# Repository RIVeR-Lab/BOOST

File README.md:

# BOOST: Battery-Swapping Multi-Agent System for Sustained Operation of Large Planetary Fleets

## Abstract
We propose a novel, heterogeneous multi-agent architecture that miniaturizes rovers by outsourcing power generation to a central hub. By delegating power generation and distribution functions to this hub, the size, weight, power, and cost (SWAP-C) per rover are reduced, enabling efficient fleet scaling. As these rovers conduct mission tasks around the terrain, the hub charges an array of replacement battery modules. When a rover requires charging, it returns to the hub to initiate an autonomous docking sequence and exits with a fully charged battery. This confers an advantage over direct charging methods, such as wireless or wired charging, by replenishing a rover in minutes as opposed to hours, increasing net rover uptime.

This work shares an open-source platform developed to demonstrate battery swapping on unknown field terrain. We detail our design methodologies utilized for increasing system reliability, with a focus on optimization, robust mechanical design, and verification. Optimization of the system is discussed, including the design of passive guide rails through simulation-based optimization methods which increase the valid docking configuration space by 258%. The full system was evaluated during integrated testing, where an average servicing time of 98 seconds was achieved on surfaces with a gradient up to 10°. We conclude by briefly proposing flight considerations for advancing the system toward a space-ready design. In sum, this prototype represents a proof of concept for autonomous docking and battery transfer on field terrain, advancing its Technology Readiness Level (TRL) from 1 to 3.
## Building the system
[CAD models are available](https://river-lab.github.io/BOOST/CAD.html) in a wide variety of data formats. The mechanical hardware primarily consists of COTS components, 3D prints, and two large sheet metal plates; a [bill of materials](https://river-lab.github.io/BOOST/BOM.html) indicates what components were utilized. For the circuitry, [electronic schematics](https://river-lab.github.io/BOOST/ELECTRONICS.html) and [custom PCBs](electrical/) are both accessible.

## Installing Software
A [software overview](https://river-lab.github.io/BOOST/CODE.html) is provided. Further instructions can be found at [SOFTWARE.md](SOFTWARE.md).

## Links
- [Demo Video](https://www.youtube.com/watch?v=pb5BIy4iOmw)
- [Website](https://river-lab.github.io/BOOST/)
- [Paper (IEEEXplore)](https://ieeexplore.ieee.org/document/10521295)
- [Preprint (ArXiV)](https://arxiv.org/abs/2401.08497)

## Citing this work
```bibtex
@INPROCEEDINGS{10521295,
  author={Holand, Ethan and Homer, Jarrod and Storrer, Alex and Khandeker, Musheeera and Muhlon, Ethan F. and Patel, Maulik and Vainqueur, Ben-oni and Antaki, David and Cooke, Naomi and Wilson, Chloe and Shafai, Bahram and Hanson, Nathaniel and Padır, Taşkın},
  booktitle={2024 IEEE Aerospace Conference}, 
  title={Battery-Swapping Multi-Agent System for Sustained Operation of Large Planetary Fleets}, 
  year={2024},
  volume={},
  number={},
  pages={1-15},
  keywords={Wireless communication;Rails;Prototypes;Optimization methods;Batteries;Outsourcing;Reliability},
  doi={10.1109/AERO58975.2024.10521295}}
```

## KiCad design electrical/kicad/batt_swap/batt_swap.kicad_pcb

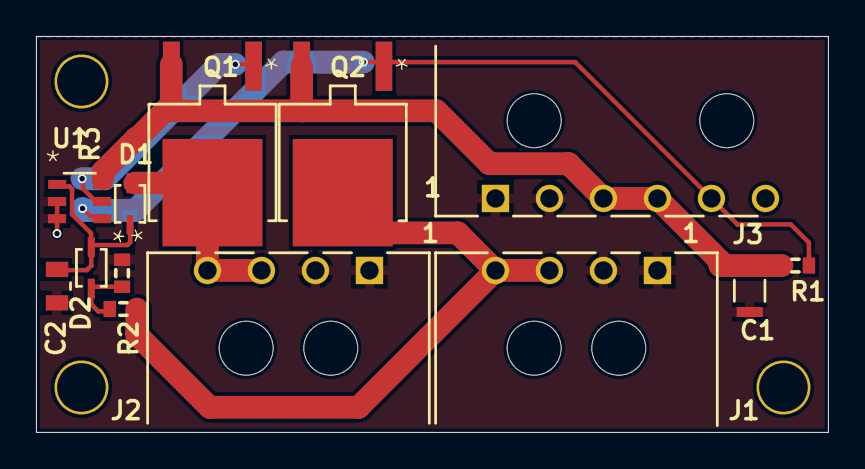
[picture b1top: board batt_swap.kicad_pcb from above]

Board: 2 copper layers, 44.0 x 22.0 mm, 13 parts (0 on the bottom side), 8 nets.

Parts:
C1: C2012JB1V226M125AC; CAP_2012_TDK
C2: CL21B105KBFNNNE; CAP_CL21_SAM
D1, D2: SD103AWS-7-F; SOD323_DIO
J1, J2: 436500400; CON_436500400_MOL
J3: 436500600; CON_436500600_MOL
Q1, Q2: AOD407; TO252_AOS
R1, R2, R3: Res3; J1-0603
U1: LTC4412ES6#TRPBF; LTC4412ES6#TRPBF_ADI

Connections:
GND: C1.1, C2.1, J1.1, J1.2, J2.1, J2.2, J3.1, J3.2, R3.1, U1.2, U1.3
NetC2_2: C2.2, D1.1, D2.1, U1.1
NetD2_2: D2.2, R2.1, R3.2
NetQ1_1: Q1.1, U1.5
batt: D1.2, J2.3, J2.4, Q1.3
hub: J1.3, J1.4, Q2.3, R2.2
stat: J3.5, Q2.1, R1.1, U1.4
vout: C1.2, J3.3, J3.4, Q1.2, Q2.2, R1.2, U1.6

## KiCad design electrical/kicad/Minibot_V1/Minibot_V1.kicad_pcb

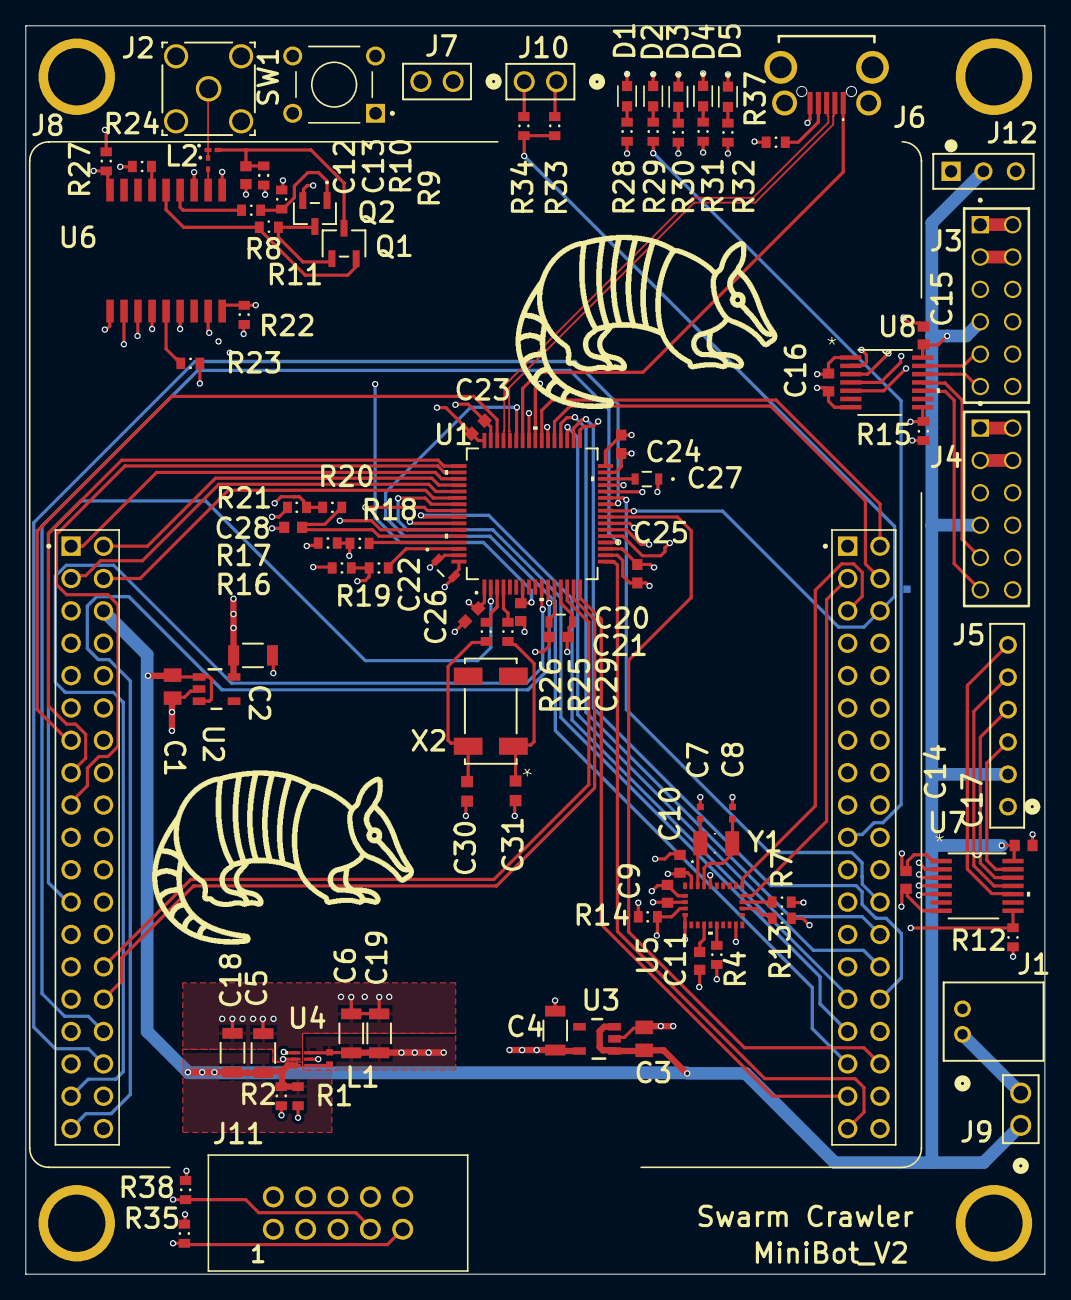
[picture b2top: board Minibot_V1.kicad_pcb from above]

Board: 6 copper layers, 80.0 x 98.0 mm, 97 parts (0 on the bottom side), 97 nets.

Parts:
C1, C3: GRM21BR71C475KE51L; CAP_GRM0805_2X1P25_MUR
C2, C4, C5, C6: CL31B106KOHNNWE; CAP_CL31_SAM
C7, C8: CBR04C220F5GAC; CAPC10555_55N_KEM
C9, C10, C11, C13, C14, C15, C16, C17: 0603; 1608[0603]
C12: C0603C0G1E270J030BA; CAP_0603_TDK
C18, C19: no stuff; CAP_CL31_SAM
C20: C1608X5R1C105K080AA; CAP_1608_TDK
C21, C23, C24, C25, C26: CC0603KRX7R7BB104; CC0603N_YAG
C22: C1608X5R1C475K080AC; CAP_1608_TDK
C27: C1608X5R1C225K080AB; CAP_1608_TDK
C28, C29: Cap Semi; 1608[0603]
C30, C31: GRM1885C1H4R3BA01D; CAPC1608X90N
D1, D2, D3, D4, D5: 150060SS75000; LED_150060SS75000
J1: S2B-PH-K-S(LF)(SN); CONN_S2B-PH-K-S_JST
J2: RF2-04A-T-00-50-G; CONN_RF2-04A-T-00-50-G_ADM
J3, J4: TSW-106-07-F-D; SAMTEC_TSW-106-07-F-D
J5: TSW-106-14-F-S; CON6_1X6_TU_TSW
J6: MCR-B-S-RA-SMT-CS14-T_R; MCRBSRASMTCS14TR
J7, J9, J10: 61300211121; CONN_61300211121_WRE
J8: NUCLEO-F446RE; MODULE_NUCLEO-F446RE
J11: 61201021621
J12: 22284036; 22-28-4036_MOL
L1: 1239AS-H-1R0M=P2; CAPC10555_55N_KEM
L2: MLG0603S36NJT000; IND_0603_TDK
Q1: AO3407A; SOT-23-3L_AOS
Q2: SMMBT3904LT1G; SOT-23-3_1P4X3P040_ONS
R1, R2, R4, R7, R8, R9, R10, R11, R12, R13, R14, R15, R16, R17, R18, R19, R20, R21, R27: 0603; J1-0603
R22, R23, R24, R25, R26, R28, R29, R30, R31, R32, R33, R34, R35, R37, R38: Res3; J1-0603
SW1: 1825910-2; TE_1825910-2
U1: STM32F446RCT6TR; LQFP64-10x10mm
U2, U3: LP2981-33DBVR; DBV0005A_N
U4: MP2148GQD-33-Z; QFN-1p0x1p5_MNP
U5: BNO055; QFN_BNO055_BOS
U6: GPS_FN; SL871
U7, U8: TXB0104PWR; PW14
X2: ABS25-32.768KHZ-1-T; ABS25-32.768KHZ-1-T_ABR
Y1: ECS-.327-12.5-34B-C-TR; XTAL_ECS-.327-12.5-34B-C-TR

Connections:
1PPS_GPS: J8.CN7_3, U1.53, U6.4
3V3: C6.2, C14.2, C16.2, C19.2, C20.2, C21.2, C22.2, C23.2, C24.2, C25.2, C26.2, J11.10, L1.2, R16.2, R17.2, R21.2, R35.2, U1.1, U1.13, U1.19, U1.32, U1.48, U1.64, U4.6, U7.1, U8.1
3V3_GPS: C2.2, R22.2, R24.1, U2.5, U6.6, U6.8
3V3_IMU: C4.2, C9.2, C10.2, R4.2, R14.2, U3.5, U5.3, U5.28
5V: C1.2, C3.2, C5.2, C15.2, C17.2, C18.2, J3.07, J4.07, J5.2, J8.CN7_6, J9.1, J12.A2, R1.2, R2.1, U2.1, U2.3, U3.1, U3.3, U4.3, U7.14, U8.14
ANT: C12.1, J2.1, L2.1
BATT_VIN: J10.1, R33.1
BATT_VOL: J8.CN10_6, R33.2, R34.1, U1.25
BOOT_IMU: J8.CN10_22, R14.1, U1.28, U5.4
D_N: J6.2, U1.44
D_P: J6.3, U1.45
ENC_1_A_5V: J3.09, U8.13
ENC_1_B_5V: J3.11, U8.12
ENC_2_A_5V: J4.09, U8.11
ENC_2_B_5V: J4.11, U8.10
FORCE_ON_N: J8.CN7_4, R27.2, U1.54, U6.18
GND: C1.1, C2.1, C3.1, C4.1, C5.1, C6.1, C7.2, C8.2, C9.1, C10.1, C11.1, C13.1, C14.1, C15.1, C16.1, C17.1, C18.1, C19.1, C20.1, C21.1, C22.1, C23.1, C24.1, C25.1, C26.1, C27.1, C28.1, C29.1, C30.2, C31.2, D1.1, D2.1, D3.1, D4.1, D5.1, J1.2, J2.2, J2.3, J2.4, J2.5, J3.05, J4.05, J5.1, J6.5, J6.MH1, J6.MH2, J6.MH3, J6.MH4, J7.2, J8.CN7_8, J8.CN7_19, J8.CN7_20, J8.CN7_22, J8.CN10_9, J8.CN10_20, J10.2, J11.2, J11.6, J11.8, J12.A3, Q2.2, R7.1, R9.1, R10.1, R12.1, R13.1, R15.1, R23.1, R27.1, R34.2, R37.1, R38.1, SW1.3, U1.12, U1.18, U1.31, U1.47, U1.63, U2.2, U3.2, U4.2, U5.2, U5.5, U5.6, U5.25, U6.1, U6.10, U6.12, U7.7, U8.7
I2C1_SCL_IMU: J8.CN10_3, R17.1, R18.2, U5.19
I2C1_SDA_IMU: J8.CN10_5, R16.1, R19.2, U5.20
ID: J6.4, R37.2
INT_IMU: J8.CN10_23, U1.41, U5.14
LED_1: J8.CN10_1, R28.1, U1.40
LED_2: J8.CN10_19, R29.1, U1.38
LED_3: J8.CN10_2, R30.1, U1.39
LED_4: J8.CN10_4, R31.1, U1.37
LED_5: J8.CN10_16, R32.1, U1.33
MOTOR_1_N: J3.03, J3.04
MOTOR_1_P: J3.01, J3.02
MOTOR_2_N: J4.03, J4.04
MOTOR_2_P: J4.01, J4.02
MOTOR_IN1: J5.3, U7.13
MOTOR_IN2: J5.4, U7.12
MOTOR_IN3: J5.5, U7.11
MOTOR_IN4: J5.6, U7.10
MOT_1A_3V3: J8.CN10_13, U1.22, U7.2
MOT_1B_3V3: J8.CN10_15, U1.23, U7.3
MOT_2A_3V3: J8.CN10_17, U1.58, U7.4
MOT_2B_3V3: J8.CN7_21, U1.59, U7.5
NRST: C29.2, SW1.1, U1.7
NetC7_1: C7.1, U5.27, Y1.2
NetC8_1: C8.1, U5.26, Y1.1
NetC11_2: C11.2, U5.9
NetC12_2: C12.2, U6.11
NetC13_2: C13.2, L2.2, Q1.3, R10.2
NetC27_2: C27.2, U1.30
NetC28_2: C28.2, R20.2, U1.60
NetC30_1: C30.1, R26.2, X2.4
NetC31_1: C31.1, R25.2, X2.1
NetD1_2: D1.2, R28.2
NetD2_2: D2.2, R29.2
NetD3_2: D3.2, R30.2
NetD4_2: D4.2, R31.2
NetD5_2: D5.2, R32.2
NetJ1_1: J1.1, J9.2
NetJ7_1: J7.1, R20.1, R21.1
NetL1_1: L1.1, U4.4
NetQ1_1: Q1.1, Q2.3, R11.1
NetQ1_2: Q1.2, R11.2, U6.14
NetQ2_1: Q2.1, R8.1, R9.2
NetR4_1: R4.1, U5.11
NetR7_2: R7.2, U5.18
NetR8_2: R8.2, U6.13
NetR18_1: R18.1, U1.61
NetR19_1: R19.1, U1.62
NetR23_2: R23.2, U6.5
NetR24_2: R24.2, U6.15
NetR25_1: R25.1, U1.4
NetR26_1: R26.1, U1.3
OE_ENC: J8.CN10_29, R15.2, U1.57, U8.8
OE_MOT: J8.CN10_27, R12.2, U1.56, U7.8
PA2: J8.CN10_35, U1.16
PA3: J8.CN10_37, U1.17
PA4: J8.CN7_32, U1.20
PB0: J8.CN7_34, U1.26
PB1: J8.CN10_24, U1.27
PB10: J8.CN10_25, U1.29
PB13: J8.CN10_30, U1.34
PB14: J8.CN10_28, U1.35
PB15: J8.CN10_26, U1.36
PC2: J8.CN7_35, U1.10
PC3: J8.CN7_37, U1.11
PC4: J8.CN10_34, U1.24
PC13: J8.CN7_23, U1.2
PG: R2.2, U4.1
RESET_N_GPS: J8.CN7_17, R22.1, U1.50, U6.9
SERVO_PWM: J8.CN10_33, J12.A1, U1.43
SWCLK: J8.CN7_15, J11.7, R38.2, U1.49
SWDIO: J8.CN7_13, J11.9, R35.1, U1.46
SW_REG_EN: R1.1, U4.5
S_ADDR_IMU: R13.2, U5.17
TIM2_CH1_ENC_1A: J8.CN10_11, U1.21, U8.2
TIM2_CH2_ENC_1B: J8.CN10_31, U1.55, U8.3
TIM5_CH1_ENC_2A: J8.CN7_28, U1.14, U8.4
TIM5_CH2_ENC_2B: J8.CN7_30, U1.15, U8.5
UART3_RX_GPS: J8.CN7_1, U1.51, U6.3
UART3_TX_GPS: J8.CN7_2, U1.52, U6.2
VBUS: J6.1, U1.42

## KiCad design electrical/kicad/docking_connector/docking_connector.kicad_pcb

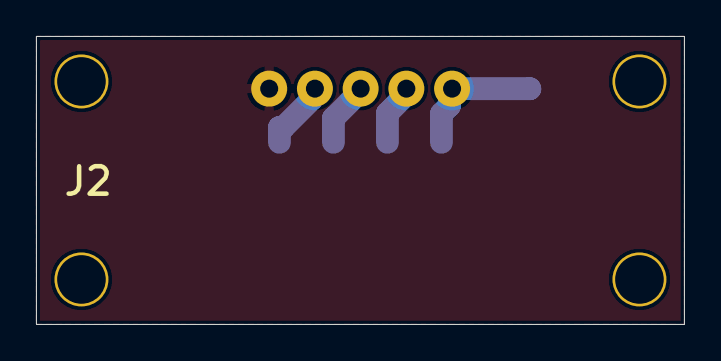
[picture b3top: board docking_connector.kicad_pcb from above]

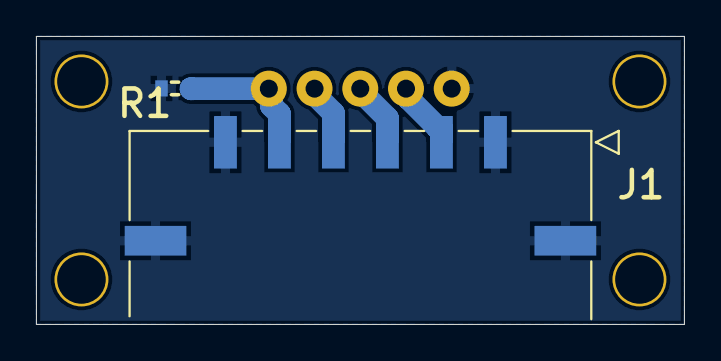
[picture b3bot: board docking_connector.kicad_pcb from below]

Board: 2 copper layers, 36.0 x 16.0 mm, 3 parts (2 on the bottom side), 5 nets.

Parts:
J1: 436500612; CON_436500612
J2: 5413
R1: Res3; J1-0603

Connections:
GND: J1.1, J1.6, J1.P1, J1.P2, J2.1, R1.1
NetJ1_2: J1.2, J2.2
NetJ1_3: J1.3, J2.3
NetJ1_4: J1.4, J2.4
NetJ1_5: J1.5, J2.5, R1.2

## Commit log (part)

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2023-01-22 pls work
2023-01-22 added some notes
2023-01-22 Add basic imu code with adafruit BNO055 library
2023-01-22 busio
2023-01-22 Rename Dir
2023-01-22 Remove cube proj
2023-01-22 Add nucleo f446re
2023-01-22 Add variants dir
2023-01-22 Copy F466R variant from platformio stm32duino
2023-01-22 Move logging to utils dir
2023-01-22 Rename variant files
2023-01-22 Remove manta stuff
2023-01-22 Add back logging macros
2023-01-22 power
2023-01-23 Remove dead code
2023-01-23 Antaki stash
2023-01-25 gps and imu rlc
2023-01-26 init software folder
2023-01-26 Add f767zi profile
2023-01-26 Fix f446re json board def
2023-01-26 Printing over usart from usb working
2023-01-26 Add rosserial
2023-01-26 Move rosserial to outside src/
    So that all of it doesn't get auto builded
2023-01-26 Add micro ros
2023-01-26 Add main.cpp with micro ros example
2023-01-26 Add compiled rosserial_arduino ros_lib
    Created by following this
    http://wiki.ros.org/rosserial_arduino/Tutorials/Arduino%20IDE%20Setup
    Section 2.
    Used WSL ubuntu.
2023-01-26 Move ros_lib to src/
2023-01-26 Add rosserial hello world example
    Fix include dir.
    Building now.
2023-01-26 adding 3d models for the robot, creating file structure
2023-01-30 Printing out on microUSB with f446re
2023-01-30 Add rosserial support for F7 series
2023-01-30 Rename that main.cpp to rosserial
2023-01-30 Copy main.cpp for trying microros
2023-01-30 Printing over serial2 working
2023-01-31 Update readme with setup and commands I used to get data from MCU to ROS2
    So i don't forget
2023-01-31 Publishing data to topic working
2023-01-31 Add a previous main.cpp backup
2023-02-02 jarrod look at 5V trace and power pours
2023-02-03 adding install directory
2023-02-04 no errors?
2023-02-04 silk
2023-02-06 armadillo
2023-02-07 mech layer
2023-02-07 botom sil
2023-02-07 Add jetson nano setup scripts
2023-02-07 Move ros comms stuff to seperate files
2023-02-09 Only publish if MCU is connected to ros node
2023-02-09 Remove the node.connected() check
    It broke the publishing.
2023-02-11 Getting twist messages working
2023-02-12 Using jlink and rosserial working again
2023-02-12 Move main.cpp to RealMain
    ROS chatter still working
2023-02-12 unicycle model to diff drive model working
2023-02-12 Add ros2 setup
2023-02-12 Move dirs
2023-02-12 Remove moved dirs
2023-02-12 Re-arrange ros launch files
2023-02-12 Update reademe
2023-02-18 create docking connector project and documents
2023-02-20 new holes
2023-02-23 Complted Nav2 Stack, along with lots of other updates.
2023-02-24 Add jarrods script
2023-02-24 Copy Encoder Library becuase need to edit it
2023-02-24 Remove arduino encoder library because using STM32Encoder
2023-02-24 adding bash scripts, organizing file structure
2023-02-24 removing unecessary folders
2023-02-25 adding realsense
2023-02-25 fixing realsense package
2023-02-25 renamed package
2023-02-25 Added a initialization to the jetson setup script
2023-02-25 updating scripts
2023-02-25 adding some git ignore stuff
2023-02-25 adding functionality to setup scripts
2023-02-27 Navigate to Aruco V1 Completed. Migrated back to ROS Galactic.
2023-02-28 Add a fakeThread class
2023-02-28 Add imu and encoder code
    IMU reading out, not sure if correct
2023-02-28 Add adafruit librarys
    Need to change double to float as f466 only has single precision FPU
2023-02-28 Add code for publishing IMU data
2023-02-28 Add examples for IMU data to ros
2023-02-28 Was publishing wrong msg... derp
2023-02-28 Publishing IMU data working now
2023-03-01 Stuff
2023-03-01 pre-merge changes
2023-03-01 Fix roshandler stuff not working becuase I didn't have config.h included derp...
2023-03-01 Add messages when looping so I know what code is runnning
2023-03-01 Change dirs
2023-03-01 Publishing to ros from nucleo working again
    Can't have logging on when using rosserial
2023-03-01 Remove logging from pio ini
2023-03-01 Separate out ROS logging and console logging
2023-03-01 idk workspace crap
2023-03-01 Fix different loop delays
2023-03-01 Fix loop delay
2023-03-03 Add commands for rosserial and ros1 bridge
2023-03-03 edited readme
2023-03-03 added some additional info to the README.
2023-03-04 added a networking script to launch roscore, ros1&ros2 bridge, and rosserial on jetson
2023-03-04 updating scripts to setup a new jetson
2023-03-08 Allow plotting with TelePlot
    Communicating with BNO055 breakout working.
2023-03-08 Add units and remove unused branch
2023-03-08 Add data_analysis files
2023-03-08 Reocrd data working
2023-03-08 Add power spectral density plotting
2023-03-08 update psd
2023-03-08 Update IMU code
2023-03-08 Add encoder manager
2023-03-12 Record data stuff
2023-03-12 Change to galactic
2023-03-12 Compiling now with IMU
    There was an imu name collision somewehre
2023-03-12 Data
2023-03-12 Remove fakethread
2023-03-12 Add fakethread.h back
    It was be problematic with git for some reason
2023-03-12 get rid of boolean to remove warning
2023-03-12 Add Arduin oEncoder lib
2023-03-12 Encoder reading working with Arduino Encoder library
2023-03-12 CubeMX generated code
2023-03-12 Add publisher for encoder data
2023-03-14 Reading in encoders working through PCB
2023-03-14 Change names
2023-03-14 Reorganize lots of things
2023-03-14 Remove old timer based encoder counting
    Didn't get it to work
2023-03-14 Metadata
2023-03-14 Change roshandler to rosmanager
2023-03-14 Chagne file names
2023-03-15 Move to folders
2023-03-15 Add folders to includes
2023-03-15 Reorganize driving commanding to separate classes and functions
2023-03-15 GPS data getting received correctly now
2023-03-15 local changes to repo prior to pushing from jetson
2023-03-15 minibot rdrive to aruco fixes.
2023-03-15 adding command to navigate to charging dock
2023-03-15 added permissions to allow executing go_to_charging_dock on base station laptop
2023-03-15 Add user jetson to dialout group
    So that it can access tty devices
2023-03-15 Copy over tinygps from zephyr repo
2023-03-15 move to data analysis
2023-03-15 Add my own ringbuffer
2023-03-15 GPS reading in and decoding the NMEA messages working
2023-03-15 Add to rosMsg to GPS and add covariance calculation
2023-03-15 Remove dead code and format
2023-03-16 Add publisher for GPS Data
2023-03-16 fine tuning for aruco docking
2023-03-18 adding executable permissions to the hub launch script
2023-03-18 adding info to the readme about networking
2023-03-20 Cmd_vel working again.
    Change consol logging to UART6.
    Change variable names.
    Put LOGs in all inits().
2023-03-20 Make folder of known stable/working firmwares
2023-03-20 Update wheelbase and wheel radius measurements
2023-03-20 Lots of things
    Reorg fails.
    Make init() header and footer macros.
    Remove old files.
2023-03-20 Need a newline at end of file
2023-03-20 move utils.h
2023-03-20 Add logging version
    Build timestamp and SHA
2023-03-20 Fix logging version
2023-03-20 Add LED pins
2023-03-20 Update pins
2023-03-20 Fix version logging to ros
2023-03-20 Colon
2023-03-22 Add script for controlling grbl through python
    Sending cmds is working
2023-03-23 Stuff working more
2023-03-24 Add lots of things
2023-03-24 Format
2023-03-24 homeing working and then moving to first empty slot
2023-03-24 Full batt swap sequence workign
2023-03-24 Increase IMU publishing freq to 40hz
2023-03-24 Add known good firmwares
2023-03-24 Add version label
2023-03-24 Add firmwares
2023-03-24 Chagne dir name
2023-03-30 Adding changes that have been on the minibot. updated nav2 driving and other things.
2023-03-30 ADd requirements
2023-03-30 Add to gitignore
2023-03-30 Change com port
2023-03-31 Add hubbot setup script
2023-03-31 Add getting come port by vid and pid
2023-03-31 dir invert
2023-03-31 Dir port
2023-03-31 Working better
2023-03-31 Swapping all 3 batteries now over and over
2023-03-31 Renam file
2023-03-31 Change heieghts
2023-04-02 Charge controller starter code
    input wokring
2023-04-02 Settup script
2023-04-02 Mostly working continuity checks
2023-04-03 Trying to make stuff work
2023-04-03 Decrease feed rates
2023-04-03 Move to folder
2023-04-03 Copy firmware from minibot firmware
2023-04-03 Parsing serial data from nucleo working
2023-04-03 Send data in oneline
2023-04-03 Getting and using continuity on batt0 working
2023-04-03 UPdate VID and PID
2023-04-05 Add getting battery voltage
    working
2023-04-05 Publishging battery state to ROS working
2023-04-05 Encoder working again.
    I disabled a needed module by accident
2023-04-06 Reading from ARduinou nano working
2023-04-06 Reorg into classes
2023-04-06 Charging when battery detected working
2023-04-06 Implement the lift being a bit higher or lower when swpping batteries in.
2023-04-08 Add hub voltage monitoring firmwares
2023-04-08 Trying things (stash)
2023-04-08 Add hubbot variant
2023-04-08 Add hubbot board file
2023-04-08 Make configs separate for minibot and hubbot
2023-04-08 GPS publishing to ros now
2023-04-08 Add working hubbot firmwar
2023-04-08 add minibot1 prefix to rostopics
2023-04-08 Create ros2_workspace for hub and python package
2023-04-08 Basic pubsub example working
2023-04-08 Remove log dir
2023-04-08 Move firmware into dir
2023-04-08 Remove build dir
2023-04-08 Move into dir
2023-04-08 Rename package
2023-04-08 Change package name
2023-04-08 Change file names
2023-04-08 adding changes to sync together nav2 and the aruco docking code.
2023-04-08 Move hubbot control scripts to ros2_ws
2023-04-08 Add started of shared statutes
2023-04-08 Add readme to shared data
2023-04-08 Publishing hub status working
2023-04-08 Use macro and change name to minibot_a
2023-04-08 Add firmware release
2023-04-08 Change dir name to minibot_a
2023-04-08 Change dir names
2023-04-08 Move control files into node package
2023-04-08 Some state machine type code
2023-04-08 Update bot_stats
2023-04-08 Readme for my commands
2023-04-08 Update start script to only by the one node
2023-04-08 Update bot stats
2023-04-08 Add hubstat
2023-04-09 integration commit
2023-04-09 small change
2023-04-09 new changes
2023-04-09 Add wing power transfer control
2023-04-09 Add to state machine
2023-04-09 Fix bugs
2023-04-09 Add delays before turning on power
2023-04-09 fixed docking sequencing adn finite state machine
2023-04-09 Dead comment
2023-04-10 functional docking code, require sindicating batttery is low, and hub wants us to dock
2023-04-10 Use continuity checking now for identifying empty and non-empty batt slots
    Also fix homing issue. Before I would set the home position while the indexer was not at its home position because it use to always start with the left slot as the empty one which meant the indexer w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
2023-04-10 Continuous operation working!!!!!!!!
    Home on axis_control init.
    Add printing more info.
2023-04-10 Fix bug
2023-04-10 ADd trying to control leds
2023-04-10 successful docking test!
2023-04-11 Cahnge BPS
2023-04-17 Decrease speeds
2023-04-17 Don't home axes when initting
    Home when initting main ros node
2023-04-17 Move to diff dirs
2023-04-17 Turn on imu on hubbot
2023-04-17 Move dirs and delete unused firmware
2023-04-17 Add a build for minibot_b
2023-04-17 Add firmwares for minibot_b
2023-04-18 Organize
2023-04-18 Add to readme
2023-04-18 Move to electrical folder
2023-10-11 Initial Website
2023-10-11 Added code and schematic placeholder pages
2023-10-12 Added CAD embeds
2023-10-12 rebuild pages
2023-10-12 updating readme and license.
2023-10-12 fixed readme
2023-10-12 adding software details to website
2023-10-12 updating titles
2023-10-12 Fixed schematics
2023-11-15 Update index.md
    Fixed symbol formatting
2024-02-01 Update index.md
    Revised author list and abstract. Added publication information.
2024-03-04 Update ELECTRONICS.md
    Fixed typos
2024-03-07 Added bill of materials
2025-06-22 Update index.md
    Update author links, add IEEEXplore link, and include citations
2025-06-22 Update _config.yml
    Add IEEEXplore link to sidebar
2025-06-22 Update index.md
    Correct title link syntax
